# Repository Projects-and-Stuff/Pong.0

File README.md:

# Pong.0 #
#### Capacitive Sensing Beer Pong Gaming Modules ####

Currently developing the prototype of a capacitive-sensing Beer Pong game module.

---

*File Structure*

* ./BPS_Test/ --> The initial Testing board, including Hardware and Firmware folders
* ./Firmware/ --> Firmware for the project (Written in C Utilizing AVR Studio 6 and AVRGCC)
* ./Hardware/ --> KiCad Project for Pong.0 Hardware
* ./GerberOutput/ --> The latest Gerber Files for manufacture
* ./Notes/ --> Project Notes, BOM, and Research

---

Additional information, research, and notes can be found at http://www.projectsandstuff.com, or email us at support@projectsandstuff.com

Let us know if you fork and make improvements. We'd be glad to consider merges that improve this project.

---

UPDATES:

---

CURRENT AUTHORS:

> [Jack Linke](http://www.jacklinke.com)
jacklinke@gmail.com

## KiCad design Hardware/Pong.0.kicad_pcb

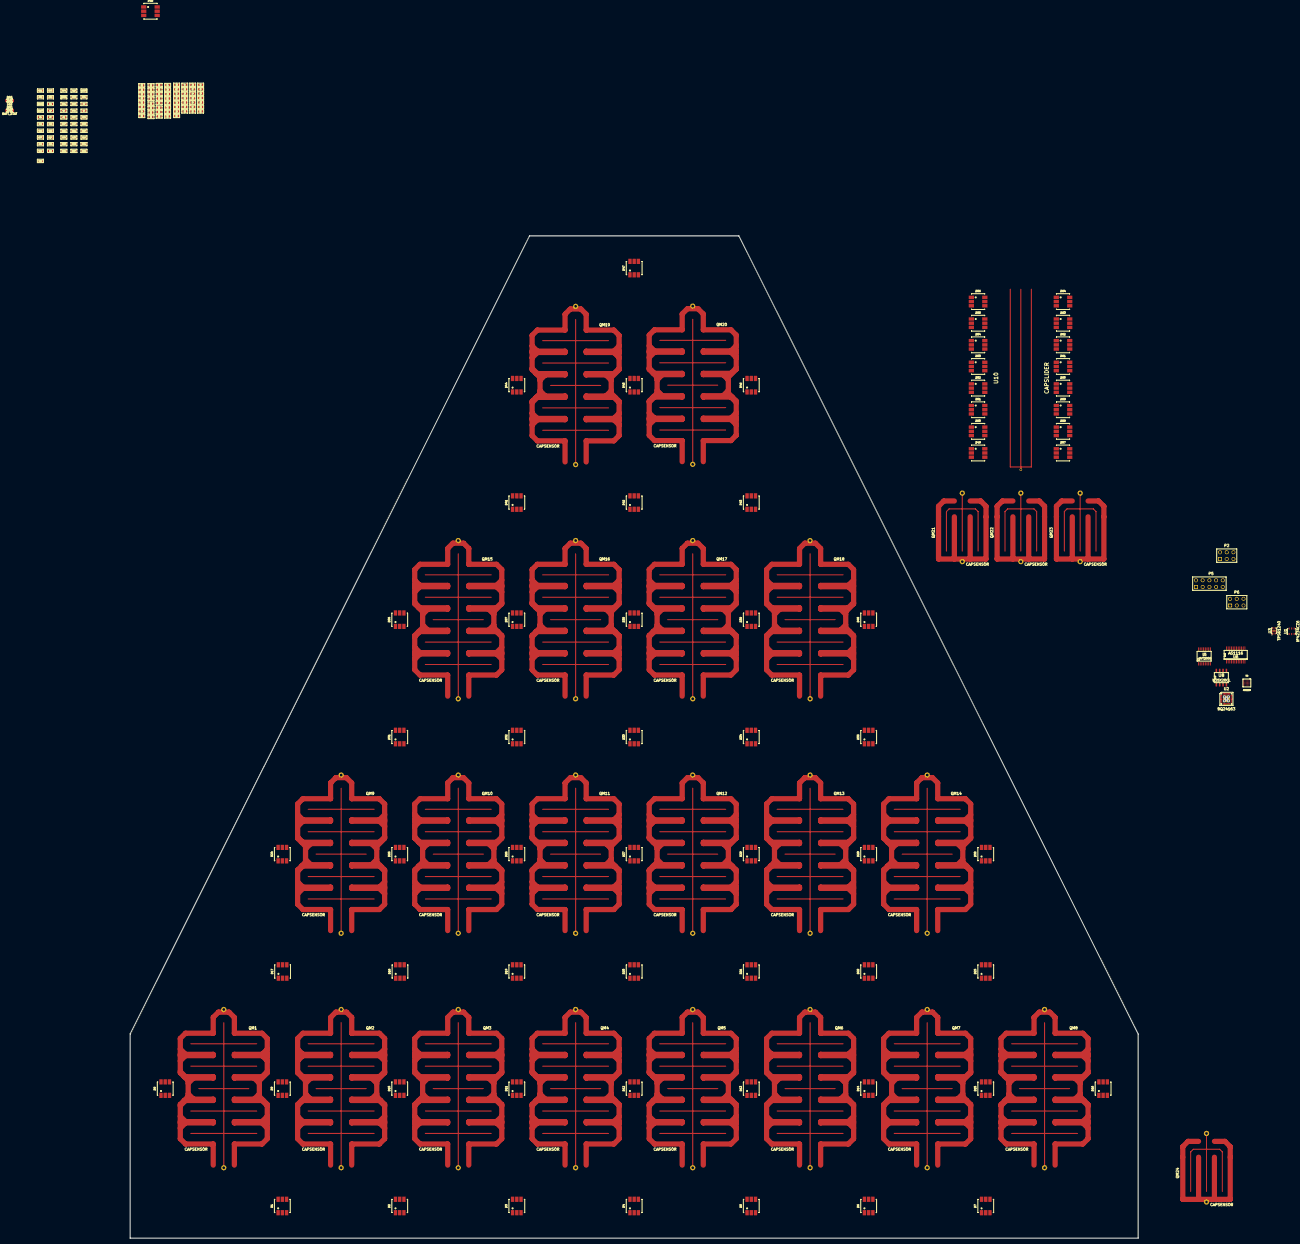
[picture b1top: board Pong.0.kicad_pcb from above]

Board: 2 copper layers, 382.2 x 380.0 mm, 213 parts (0 on the bottom side), 94 nets, no tracks yet.

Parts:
C1: 4.7nF; SM0603
C2, C3, C6, C9, C19, C20, C48: 1uF; SM0603
C4, C5, C11, C12: 4.7uF; SM0603
C7: 0.01uF; SM0603
C8, C13, C15, C17, C44, C51, C58: 10uF; SM0603
C10: CSMALL; SM0603
C14, C16, C18, C43, C45, C46, C47, C52, C53, C54, C55, C56, C57, C59, C60: 0.1uF; SM0603
C21: 2.2uF; SM0603
C22, C23, C24, C25, C26, C27, C29, C30, C31, C32, C33, C34, C36, C37, C38, C39, C40, C41: 1nF; SM0603
C49, C50: 15pF; SM0603
CS0, CS1, CS2, CS3: 4.7nF; SM0603
D1, D2, D3, D4, D5, D6, D7, D8, D9, D10, D11, D12, D13, D14, D15, D16, D17, D18, D19, D20, D21, D22, D23, D24, D25, D26, D27, D28, D29, D30, D31, D32, D33, D34, D35, D36, D37, D38, D39, D40, D41, D42, D43, D44, D45, D46, D47, D48, D49, D50, D51, D52, D53, D54, D55, D56, D57, D58, D59, D60, D61, D62, D63, D64: RGB_LED_V2; PLCC-5050
D65: BATT_STAT; LED-0805
D66: LED; LED-0805
P2: ISP; pin_array_3x2
P5: JTAG; PIN_ARRAY_5x2
P6: PDI; pin_array_3x2
QM1, QM2, QM3, QM4, QM5, QM6, QM7, QM8, QM9, QM10, QM11, QM12, QM13, QM14, QM15, QM16, QM17, QM18, QM19, QM20: CAPSENSOR; Capsensor_35mm_x_60mm
QM21, QM22, QM23, QM24: CAPSENSOR; CapSensor_20mm_x_24mm
R1: 1M; SM0603
R2, R23: R; SM0603
R3: R_HI; SM0603
R4: R_LO; SM0603
R5, R6, R7, R9, R10, R11, R12, R22, R24, R26, R27, R28: 10k; SM0603
R8: 100k; SM0603
R13, R14, R15, R16, R18, R19, R20, R21: 560; SM0603
R17: 200k; SM0603
R25: R_SMALL; SM0603
RS1, RS2, RS3, RS4, RS5, RS6, RS7: 1k; SM0603
RSMP0, RSMP1, RSMP2, RSMP3: 470k; SM0603
RX0, RX1, RX2, RX3, RX4, RX5, RX6, RX7: 1k; SM0603
RY0, RY1, RY2, RY3: 1k; SM0603
U1: IP4234CZ6; SOT457
U2: BQ24163; QFN24
U3: TPS61240; QFN-6
U4: AS1119; WLCSP-36
U5: NVT2006; TSSOP16
U6: AS1116; SSOP24
U8: W25X20CL; SO8E
U10: CAPSLIDER; CapSensor_Slider_16mm_x_66mm

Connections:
/Controller/CTRL_3_3V: C10.1, C11.1, C14.1, C16.1, C18.1, C46.1, C48.1, C60.1, P2.2, P5.4, P6.2, R5.1, R6.1, R7.1, R13.1, R14.1, R15.1, R16.1, U2.13, U2.14, U3.4, U3.6, U4.A6, U4.E1, U4.E5, U5.16, U8.8
/Controller/CTRL_D+: U1.1, U2.2
/Controller/CTRL_D-: U1.6, U2.1
/Controller/CTRL_MISO_1: P2.1, U8.2
/Controller/CTRL_MISO_2: R14.2, U5.3
/Controller/CTRL_MOSI_1: P2.4, U8.5
/Controller/CTRL_MOSI_2: R15.2, U5.2
/Controller/CTRL_SCK_1: P2.3, U8.6
/Controller/CTRL_SCK_2: R16.2, U5.1
/Controller/CTRL_SCL_1: R7.2, U2.3
/Controller/CTRL_SDA_1: R6.2, U2.4
/Controller/CTRL_SMP: RSMP0.2, RSMP1.2, RSMP2.2, RSMP3.2
/Controller/CTRL_Y0A: CS0.1, RY0.2
/Controller/CTRL_Y0B: CS0.2, RSMP0.1
/Controller/CTRL_Y1A: CS1.1, RY1.2
/Controller/CTRL_Y1B: CS1.2, RSMP1.1
/Controller/CTRL_Y2A: CS2.1, RY2.2
/Controller/CTRL_Y2B: CS2.2, RSMP2.1
/Controller/CTRL_Y3A: CS3.1, RY3.2
/Controller/CTRL_Y3B: CS3.2, RSMP3.1
/Controller/CTRL_~SS~_1: P2.5, U8.1
/Controller/CTRL_~SS~_2: R13.2, U5.4
/Controller/PDI_CLK: P5.6, P6.5
/LED_Display/CS0: C36.1, D1.2, D1.3, D1.5, D2.2, D3.2, D4.2, D5.2, D6.2, D7.2, D8.2, D17.1, D17.3, D17.5, D33.1, D33.3, D33.5, U4.A5
/LED_Display/CS1: C38.1, D1.1, D2.3, D2.5, D17.2, D18.2, D18.3, D18.5, D19.2, D20.2, D21.2, D22.2, D23.2, D24.2, D34.1, D34.3, D34.5, U4.A4
/LED_Display/CS2: C40.1, D2.1, D3.3, D3.5, D18.1, D19.3, D19.5, D33.2, D34.2, D35.2, D35.3, D35.5, D36.2, D37.2, D38.2, D39.2, D40.2, U4.A3
/LED_Display/CS3: C29.1, D1.4, D2.4, D3.1, D3.4, D4.4, D4.5, D5.4, D6.4, D7.4, D8.4, D19.1, D20.3, D20.5, D35.1, D36.3, D36.5, U4.B4
/LED_Display/CS4: C31.1, D4.1, D4.3, D5.5, D17.4, D18.4, D19.4, D20.1, D20.4, D21.4, D21.5, D22.4, D23.4, D24.4, D36.1, D37.3, D37.5, U4.B3
/LED_Display/CS5: C33.1, D5.1, D5.3, D6.5, D21.1, D21.3, D22.5, D33.4, D34.4, D35.4, D36.4, D37.1, D37.4, D38.4, D38.5, D39.4, D40.4, U4.B2
/LED_Display/CS6: C22.1, D1.6, D2.6, D3.6, D4.6, D5.6, D6.1, D6.3, D6.6, D7.6, D8.6, D22.1, D22.3, D23.5, D38.1, D38.3, D39.5, U4.C4
/LED_Display/CS7: C24.1, D7.1, D7.3, D7.5, D17.6, D18.6, D19.6, D20.6, D21.6, D22.6, D23.1, D23.3, D23.6, D24.6, D39.1, D39.3, D40.5, U4.C3
/LED_Display/CS8: C26.1, D8.1, D8.3, D8.5, D24.1, D24.3, D24.5, D33.6, D34.6, D35.6, D36.6, D37.6, D38.6, D39.6, D40.1, D40.3, D40.6, U4.C2
/LED_Display/CS9: C37.1, D9.2, D9.3, D9.5, D10.2, D11.2, D12.2, D13.2, D14.2, D15.2, D16.2, D25.1, D25.3, D25.5, D41.1, D41.3, D41.5, U4.D4
/LED_Display/CS10: C39.1, D9.1, D10.3, D10.5, D25.2, D26.2, D26.3, D26.5, D27.2, D28.2, D29.2, D30.2, D31.2, D32.2, D42.1, D42.3, D42.5, U4.D3
/LED_Display/CS11: C41.1, D10.1, D11.3, D11.5, D26.1, D27.3, D27.5, D41.2, D42.2, D43.2, D43.3, D43.5, D44.2, D45.2, D46.2, D47.2, D48.2, U4.D2
/LED_Display/CS12: C30.1, D9.4, D10.4, D11.1, D11.4, D12.4, D12.5, D13.4, D14.4, D15.4, D16.4, D27.1, D28.3, D28.5, D43.1, D44.3, D44.5, U4.E4
/LED_Display/CS13: C32.1, D12.1, D12.3, D13.5, D25.4, D26.4, D27.4, D28.1, D28.4, D29.4, D29.5, D30.4, D31.4, D32.4, D44.1, D45.3, D45.5, U4.E3
/LED_Display/CS14: C34.1, D13.1, D13.3, D14.5, D29.1, D29.3, D30.5, D41.4, D42.4, D43.4, D44.4, D45.1, D45.4, D46.4, D46.5, D47.4, D48.4, U4.E2
/LED_Display/CS15: C23.1, D9.6, D10.6, D11.6, D12.6, D13.6, D14.1, D14.3, D14.6, D15.6, D16.6, D30.1, D30.3, D31.5, D46.1, D46.3, D47.5, U4.F4
/LED_Display/CS16: C25.1, D15.1, D15.3, D15.5, D25.6, D26.6, D27.6, D28.6, D29.6, D30.6, D31.1, D31.3, D31.6, D32.6, D47.1, D47.3, D48.5, U4.F3
/LED_Display/CS17: C27.1, D16.1, D16.3, D16.5, D32.1, D32.3, D32.5, D41.6, D42.6, D43.6, D44.6, D45.6, D46.6, D47.6, D48.1, D48.3, D48.6, U4.F2
/LED_Display_B/DIG0: D49.2, D50.2, D51.2, D52.2, D53.2, D54.2, D55.2, D56.2, U6.2
/LED_Display_B/DIG1: D57.2, D58.2, D59.2, D60.2, D61.2, D62.2, D63.2, D64.2, U6.3
/LED_Display_B/DIG2: D49.4, D50.4, D51.4, D52.4, D53.4, D54.4, D55.4, D56.4, U6.4
/LED_Display_B/DIG3: D57.4, D58.4, D59.4, D60.4, D61.4, D62.4, D63.4, D64.4, U6.5
/LED_Display_B/DIG4: D49.6, D50.6, D51.6, D52.6, D53.6, D54.6, D55.6, D56.6, U6.7
/LED_Display_B/DIG5: D57.6, D58.6, D59.6, D60.6, D61.6, D62.6, D63.6, D64.6, U6.8
/LED_Display_B/DISP_B_5V: C12.1, C45.1, R17.1, U3.2, U3.3, U6.19
/LED_Display_B/SEGA: D49.1, D49.3, D49.5, D57.1, D57.3, D57.5, U6.15
/LED_Display_B/SEGB: D50.1, D50.3, D50.5, D58.1, D58.3, D58.5, U6.17
/LED_Display_B/SEGC: D51.1, D51.3, D51.5, D59.1, D59.3, D59.5, U6.20
/LED_Display_B/SEGD: D52.1, D52.3, D52.5, D60.1, D60.3, D60.5, U6.23
/LED_Display_B/SEGE: D53.1, D53.3, D53.5, D61.1, D61.3, D61.5, U6.21
/LED_Display_B/SEGF: D54.1, D54.3, D54.5, D62.1, D62.3, D62.5, U6.16
/LED_Display_B/SEGG: D55.1, D55.3, D55.5, D63.1, D63.3, D63.5, U6.18
/LED_Display_B/SEGH: D56.1, D56.3, D56.5, D64.1, D64.3, D64.5, U6.22
/PowerManagement/VDRV: C6.1, D65.1, R3.1, U2.6
GND: C1.2, C2.2, C3.2, C4.2, C5.2, C6.2, C9.2, C10.2, C11.2, C12.2, C14.2, C16.2, C18.2, C21.1, C22.2, C23.2, C24.2, C25.2, C26.2, C27.2, C29.2, C30.2, C31.2, C32.2, C33.2, C34.2, C36.2, C37.2, C38.2, C39.2, C40.2, C41.2, C43.2, C45.2, C46.2, C47.2, C48.2, C49.2, C50.2, C52.2, C53.2, C54.2, C55.2, C56.2, C57.2, C58.2, C59.2, C60.2, P2.6, P5.2, P5.10, P6.6, R1.2, R4.2, R23.2, U1.2, U2.5, U2.15, U2.16, U2.17, U2.24, U3.1, U3.GNDP, U4.A2, U4.B5, U4.C5, U4.D5, U4.F5, U5.5, U5.6, U5.7, U5.8, U5.15, U6.6, U8.4
unnamed: C20.2, U4.D1
unnamed: C20.1, U4.A1
unnamed: C19.2, U4.C1
unnamed: C19.1, U4.B1
unnamed: C21.2, U4.F1
unnamed: C1.1, R1.1
unnamed: C9.1, U2.11, U2.12
unnamed: C5.1, U2.23
unnamed: R3.2, R4.1, U2.9
unnamed: R5.2, R8.1, U2.7
unnamed: C7.2, U2.19
unnamed: C2.1, U2.21
unnamed: R2.2, U2.8
unnamed: D65.2, R2.1
unnamed: C3.1, U1.5, U2.22
unnamed: C7.1, U2.18
unnamed: C4.1, U2.20
unnamed: QM9.Y, QM10.Y, QM11.Y, QM12.Y, QM13.Y, QM14.Y, QM15.Y, QM16.Y, RY1.1
unnamed: QM1.Y, QM2.Y, QM3.Y, QM4.Y, QM5.Y, QM6.Y, QM7.Y, QM8.Y, RY0.1
unnamed: RY3.1, U10.Y
unnamed: QM1.X, QM9.X, QM17.X, RS1.1, RX0.2, U10.X8
unnamed: QM2.X, QM10.X, QM18.X, RS1.2, RS2.1, RX1.2, U10.X7
unnamed: QM3.X, QM11.X, QM19.X, RS2.2, RS3.1, RX2.2, U10.X6
unnamed: QM4.X, QM12.X, QM20.X, RS3.2, RS4.1, RX3.2, U10.X5
unnamed: QM5.X, QM13.X, QM21.X, RS4.2, RS5.1, RX4.2, U10.X4
unnamed: QM6.X, QM14.X, QM22.X, RS5.2, RS6.1, RX5.2, U10.X3
unnamed: QM7.X, QM15.X, QM23.X, RS6.2, RS7.1, RX6.2, U10.X2
unnamed: QM8.X, QM16.X, QM24.X, RS7.2, RX7.2, U10.X1
unnamed: QM17.Y, QM18.Y, QM19.Y, QM20.Y, QM21.Y, QM22.Y, QM23.Y, QM24.Y, RY2.1
unnamed: C52.1, C53.1, C54.1, C55.1, C56.1
unnamed: C57.1, C58.1
unnamed: R18.2, U5.12, U6.14
unnamed: R20.2, U5.10, U6.24
unnamed: R19.2, U5.11, U6.1
unnamed: R21.2, U5.9, U6.11
unnamed: C43.1, R17.2, R18.1, R19.1, R20.1, R21.1, U5.13, U5.14

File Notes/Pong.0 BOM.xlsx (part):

Bill of Materials - Pong.0 - Electronics |  |  |  |  |  |  |  |  |  | # of boards goal: | 500
Projects and Stuff LLC - http://www.projectsandstuff.com
Total BOM Parts Cost: | 15529.26 | Part Cost Per Board: |  | 31.058520000000001
Description | Mfg Part # | Package | KiCad Footprint | Default Supplier | Supplier On Hand | Qty per board | Total Qty Needed | Price per part at Qty | Total Price | Notes | Part References
IC Atmel AVR XMEGA16A4U | ATXMEGA16A4U-AUR | 44-TQFP |  | DigiKey | 3483 | 1 | 500 | 2.0038999999999998 | 1001.9499999999999
IC Level Translator | NVT2006PW,118 | 16-TSSOP |  | DigiKey | 7348 | 1 | 500 | 0.49 | 245 | SPI/I2C translation for the LED Drivers
PLCC-6 RGB LED |  | 5mm x 5mm |  |  |  | 64 | 32000 | 0.04 | 1280 | LED Lighting
Capacitor Ceramic 15pF | CL10C150JB8NCNC | 0603 |  | DigiKey | 6750 | 2 | 1000 | 3.0899999999999999E-3 | 3.09 |  | C49, C50
Capacitor Ceramic 1nF | CL10B102KB8SFNC | 0603 |  | DigiKey | 24000 | 20 | 10000 | 2.3700000000000001E-3 | 23.700000000000003 |  | C22, C23, C24, C25, C26, C27, C28, C29, C30, C31, C32, C33, C34, C35, C36, C37,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
Capacitor Ceramic 4.7nF | CL10B472KB8SFNC | 0603 |  | DigiKey | 8862 | 5 | 2500 | 6.1799999999999997E-3 | 15.45 |  | C1, CS0, CS1, CS2, CS3
Capacitor Ceramic 0.01uF | CL10B103MB8NCNC | 0603 |  | DigiKey | 7910 | 1 | 500 | 2.7799999999999999E-3 | 1.39 |  | C7
Capacitor Ceramic 0.1uF 50V 10% | CL10B104KO8NNNC | 0603 |  | DigiKey | 3308000 | 15 | 7500 | 3.5899999999999999E-3 | 26.925000000000001 | Used for Power Input/Output filtering and Decoupling | C14, C16, C18, C43, C45, C46, C47, C52, C53, C54, C55, C56, C57, C59, C60
Capacitor Ceramic 1uF | LMK107B7105KA-T | 0603 |  | DigiKey | 76000 | 7 | 3500 | 7.8200000000000006E-3 | 27.37 |  | C2, C3, C6, C9, C19, C20, C48
Capacitor Ceramic 2.2uF | LMK107B7225KA-T | 0603 |  | DigiKey | 217168 | 1 | 500 | 3.8519999999999999E-2 | 19.259999999999998 |  | C21
Capacitor Ceramic 4.7uF | C1608X7S1A475M080AC | 0603 |  | DigiKey | 1179 | 4 | 2000 | 6.1199999999999997E-2 | 122.39999999999999 |  | C4, C5, C11, C12
Capacitor Ceramic 10uF | C1608X7S0J106M080AC | 0603 |  | Digikey | 4000 | 7 | 3500 | 0.26812999999999998 | 938.45499999999993 | Used for Supply Filtering (Input and Output). Low ESR | C8, C13, C15, C17, C44, C51, C58
Resistor 560 Ohm | ERJ-3GEYJ561V | 0603 |  | DigiKey | 155000 | 8 | 4000 | 1.5200000000000001E-3 | 6.08 | Cheaper to buy 5000 | R13, R14, R15, R16, R18, R19, R20, R21
Resistor 1k | MCR03EZP5J102 | 0603 |  | DigiKey | 1365000 | 18 | 9000 | 1.1999999999999999E-3 | 10.799999999999999 | Cheaper to buy 10000 | RX0, RX1, RX2, RX3, RX4, RX5, RX6, RX7, RS1, RS2, RS3, RS4, RS5, RS6, RY0, RY1,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
Resistor 10k | ERJ-3GEYJ103V | 0603 |  | DigiKey | 8283494 | 12 | 6000 | 2.5600000000000002E-3 | 15.360000000000001 |  | R5, R6, R7, R9, R10, R11, R12, R22, R24, R26, R27, R28
Resistor 100k | RC1608J104CS | 0603 |  | DigiKey | 20673 | 1 | 500 | 2.7399999999999998E-3 | 1.3699999999999999 |  | R8
Resisitor 200k | RC1608J204CS | 0603 |  | DigiKey | 20000 | 1 | 500 | 2.7399999999999998E-3 | 1.3699999999999999 |  | R17
Resistor 470k | ERJ-3EKF4703V | 0603 |  | DigiKey | 299269 | 4 | 2000 | 3.8400000000000001E-3 | 7.6800000000000006 |  | RSMP0, RSMP1, RSMP2, RSMP3
Resistor 1M | RC1608J105CS | 0603 |  | DigiKey | 12666 | 1 | 500 | 2.7399999999999998E-3 | 1.3699999999999999 |  | R1
LED Red Diffused | LH R974-LP-1 | 0805 |  | DigiKey | 43194 | 1 | 500 | 4.3700000000000003E-2 | 21.85 | Power Indicator
LED Green Diffused | LG N971-KN-1 | 0805 |  | DigiKey | 94327 | 1 | 500 | 4.3700000000000003E-2 | 21.85 | Status Indicator
IC Boost Regulator 5V 0.45A | TPS61240DRVT | 6-WDFN |  | DigiKey | 51750 | 1 | 500 | 0.9425 | 471.25 | 5V Power for LEDs and Drivers
IC 64 LED Driver | AS1116-BSST | 24-QSOP |  | DigiKey | 12727 | 1 | 500 | 3.7223600000000001 | 1861.18 | SPI LED Driver
IC LED Matrix Driver | AS1119-BWLT | 36-WLCSP |  | DigiKey | 2326 | 1 | 500 | 5.7294200000000002 | 2864.71
USB Connector | ZX62WRD-B-5PC | USB Micro B |  | DigiKey | 5213 | 1 | 500 | 0.83160000000000001 | 415.8 | Water Resistant Micro B USB Connector
IC RF Transceiver | CC2500RTKR | 20-VFQFN |  | DigiKey | 15533 | 1 | 500 | 1.56 | 780 | 2.4GHz Transceiver
26 MHz Crystal | ABM8G-26.000MHZ-4Y-T3 | 4-SMD |  | DigiKey | 6517 | 1 | 500 | 0.51300000000000001 | 256.5 | Reference Crystal for RF Chip CC2500
IC Battery Manager/Charger | BQ24163RGET | 24-VFQFN |  | DigiKey | 706 | 1 | 500 | 2.6324999999999998 | 1316.25
IC USB ESD Protection | IP4234CZ6,125 | 6-TSOP |  | DigiKey | 8164 | 1 | 500 | 0.21565999999999999 | 107.83
LI Battery |  |  |  |  |  | 1 | 500 | 7 | 3500
IC Flash Memory 2Mbit | W25X20CLSNIG | 8-SOIC |  | DigiKey | 7531 | 1 | 500 | 0.32604 | 163.02000000000001
 |  |  |  |  |  |  | 0 |  | 0
 |  |  |  |  |  |  | 0 |  | 0
 |  |  |  |  |  |  | 0 |  | 0
 |  |  |  |  |  |  | 0 |  | 0
 |  |  |  |  |  |  | 0 |  | 0
 |  |  |  |  |  |  | 0 |  | 0
 |  |  |  |  |  |  | 0 |  | 0
 |  |  |  |  |  |  | 0 |  | 0
 |  |  |  |  |  |  | 0 |  | 0
 |  |  |  |  |  |  | 0 |  | 0
 |  |  |  |  |  |  | 0 |  | 0
 |  |  |  |  |  |  | 0 |  | 0
 |  |  |  |  |  |  | 0 |  | 0
 |  |  |  |  |  |  | 0 |  | 0
 |  |  |  |  |  |  | 0 |  | 0
 |  |  |  |  |  |  | 0 |  | 0
 |  |  |  |  |  |  | 0 |  | 0
 |  |  |  |  |  |  | 0 |  | 0
 |  |  |  |  |  |  | 0 |  | 0
 |  |  |  |  |  |  | 0 |  | 0
 |  |  |  |  |  |  | 0 |  | 0
 |  |  |  |  |  |  | 0 |  | 0
 |  |  |  |  |  |  | 0 |  | 0
 |  |  |  |  |  |  | 0 |  | 0
 |  |  |  |  |  |  | 0 |  | 0
 |  |  |  |  |  |  | 0 |  | 0
 |  |  |  |  |  |  | 0 |  | 0
 |  |  |  |  |  |  | 0 |  | 0
 |  |  |  |  |  |  | 0 |  | 0
 |  |  |  |  |  |  | 0 |  | 0
 |  |  |  |  |  |  | 0 |  | 0
 |  |  |  |  |  |  | 0 |  | 0
 |  |  |  |  |  |  | 0 |  | 0
 |  |  |  |  |  |  | 0 |  | 0
 |  |  |  |  |  |  | 0 |  | 0
 |  |  |  |  |  |  | 0 |  | 0
 |  |  |  |  |  |  | 0 |  | 0
 |  |  |  |  |  |  | 0 |  | 0
 |  |  |  |  |  |  | 0 |  | 0
 |  |  |  |  |  |  | 0 |  | 0
 |  |  |  |  |  |  | 0 |  | 0
 |  |  |  |  |  |  | 0 |  | 0
 |  |  |  |  |  |  | 0 |  | 0
 |  |  |  |  |  |  | 0 |  | 0
 |  |  |  |  |  |  | 0 |  | 0
 |  |  |  |  |  |  | 0 |  | 0
 |  |  |  |  |  |  | 0 |  | 0
 |  |  |  |  |  |  | 0 |  | 0
 |  |  |  |  |  |  | 0 |  | 0
 |  |  |  |  |  |  | 0 |  | 0
 |  |  |  |  |  |  | 0 |  | 0
 |  |  |  |  |  |  | 0 |  | 0
 |  |  |  |  |  |  | 0 |  | 0
 |  |  |  |  |  |  | 0 |  | 0
 |  |  |  |  |  |  | 0 |  | 0
 |  |  |  |  |  |  | 0 |  | 0
 |  |  |  |  |  |  | 0 |  | 0
 |  |  |  |  |  |  | 0 |  | 0
 |  |  |  |  |  |  | 0 |  | 0
 |  |  |  |  |  |  | 0 |  | 0
 |  |  |  |  |  |  | 0 |  | 0
 |  |  |  |  |  |  | 0 |  | 0
 |  |  |  |  |  |  | 0 |  | 0
 |  |  |  |  |  |  | 0 |  | 0
 |  |  |  |  |  |  | 0 |  | 0
 |  |  |  |  |  |  | 0 |  | 0
 |  |  |  |  |  |  | 0 |  | 0
 |  |  |  |  |  |  | 0 |  | 0
 |  |  |  |  |  |  | 0 |  | 0
 |  |  |  |  |  |  | 0 |  | 0
 |  |  |  |  |  |  | 0 |  | 0
 |  |  |  |  |  |  | 0 |  | 0
 |  |  |  |  |  |  | 0 |  | 0
 |  |  |  |  |  |  | 0 |  | 0
 |  |  |  |  |  |  | 0 |  | 0
 |  |  |  |  |  |  | 0 |  | 0
 |  |  |  |  |  |  | 0 |  | 0
 |  |  |  |  |  |  | 0 |  | 0
 |  |  |  |  |  |  | 0 |  | 0
 |  |  |  |  |  |  | 0 |  | 0
 |  |  |  |  |  |  | 0 |  | 0
 |  |  |  |  |  |  | 0 |  | 0
 |  |  |  |  |  |  | 0 |  | 0
 |  |  |  |  |  |  | 0 |  | 0
 |  |  |  |  |  |  | 0 |  | 0
 |  |  |  |  |  |  | 0 |  | 0
 |  |  |  |  |  |  | 0 |  | 0
 |  |  |  |  |  |  | 0 |  | 0
 |  |  |  |  |  |  | 0 |  | 0
 |  |  |  |  |  |  | 0 |  | 0
 |  |  |  |  |  |  | 0 |  | 0
 |  |  |  |  |  |  | 0 |  | 0
 |  |  |  |  |  |  | 0 |  | 0
 |  |  |  |  |  |  | 0 |  | 0
 |  |  |  |  |  |  | 0 |  | 0
 |  |  |  |  |  |  | 0 |  | 0
 |  |  |  |  |  |  | 0 |  | 0
 |  |  |  |  |  |  | 0 |  | 0
 |  |  |  |  |  |  | 0 |  | 0
 |  |  |  |  |  |  | 0 |  | 0
 |  |  |  |  |  |  | 0 |  | 0
 |  |  |  |  |  |  | 0 |  | 0
 |  |  |  |  |  |  | 0 |  | 0
 |  |  |  |  |  |  | 0 |  | 0
 |  |  |  |  |  |  | 0 |  | 0
 |  |  |  |  |  |  | 0 |  | 0
 |  |  |  |  |  |  | 0 |  | 0
 |  |  |  |  |  |  | 0 |  | 0
 |  |  |  |  |  |  | 0 |  | 0
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
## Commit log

2012-03-15 First commit. Adding Readme
2012-03-15 updating initial files
2012-03-15 updating initial KiCad Project for Test Bord
2012-04-09 Adding Note Files to start low-level documentation prep
2012-04-09 Small updates to BOM. Will improve soon
2012-04-22 Updated README.md for the test board
2012-04-22 Created basic Sketchup image to describe the basic layout prior to prototyping
2012-04-22 Corrected sketch (removed an extraneous line)
2012-04-22 Began working BOM for test board, which will eventually supplement/supersede previously posted BOM for main project
2012-04-25 Started building up BOM based on known needs
2012-04-25 Began building documentation
2012-04-26 Updated Project Log. Updated BOM with additional microcontroller data
2012-04-29 Updated Project log based on most recent behind-the-scenes work
2012-04-29 Quick BOM update with details about desired battery specifications
2012-04-29 Updated the Project Log with more info about batteries
2012-04-29 Removed Charge Manager and updated Battery Specs in BOM
2012-04-29 Cleaned up Notes folder
2012-05-02 Updated BOM and Project Log with new choice of LDO regulator
2012-05-03 Major additions to BOM and began Schematics in earnest!
2012-05-03 Corrected Display matrix problem
2012-05-05 Fleshed out schematics some more. Updated Project Log and BOM
2012-05-05 Updated display matrix to better reflect final project goals
2012-05-05 Whoops - Fixed goofy mistake in the display matrix
2012-05-05 Updated Schematic PDF
2012-05-06 Updated BOM, Project Log, and Schematic PDF, and improved schematic details
2012-05-06 Updated Project Log with notes about batteries
2012-05-06 Relocated Schematic PDF to Hardware folder
2012-05-07 Added new BOM format
2012-05-12 Cleaned up Schematics
2012-05-16 Removed BOM.txt in favor of Excel formatted BOM
2012-05-17 Updated BOM with additional sheet for non-electronic parts
2012-05-19 Updated Repository name and filenames
2012-05-19 Updated more filenames and added initial firmware skeleton
2012-05-20 Slight updates to Project Log
2012-05-29 Removed BOM.txt in preference of BOM spreadsheet
2012-06-02 Updated Schematic and Project Log
2012-06-12 Updated Project Log
2012-07-04 Updated Project Log and added ATTiny84A for slider board testing
2012-07-04 Replaced ATTiny84 with ATMega168 for the added pins and peripherals
2012-08-15 Fleshed out main project, corrected errors, updated Project Log
2012-08-17 Started fleshing out slider portion of the test board schematics
2012-08-17 Forgot to include updated Project Log in last push
2012-08-20 Updated Slider and Project Log
2012-08-26 Cleaned up schematics and added footprint column to BOM. Yet to be populated
2012-09-12 Updated Schematics with LED indicators and cleanup and updated Project Log
2013-01-01 Cleaned up schematics and corrected crystal load capacitor calculation error (should be 36pF vice 9pF)
2013-01-01 Associated some parts with correct modules, and began PCB creation.
2013-01-03 Added 2 buttons and continued organizing PCB.
2013-09-02 Finally making some updates. Beginning work on requirements
2013-09-06 Updated BOM and Requirements Document
2013-09-06 Updated Schematic - Very basic so far
2013-09-06 Updated BOM and Schematic with significant components
2013-09-08 Updated Schematic with Battery Manager and updated some uC pins
2013-09-08 Added sheet for QMatrix Sensors and Sliders
2013-09-09 Added logos, continued updating schematics.
2013-09-09 Added items from Schematics to BOM.
2013-09-09 Replaced Firmware folder contents with beginning code that reflects the newer schematics.
2013-09-09 Performed first Firmware Build (not actually usable)
2013-09-12 Updated LED Display Sheet
2013-09-12 Added Slider. Imported Sheet Pins. Made other minor adjustments to schematics.
2013-09-19 Continued populating the schematics.
2013-09-19 Corrected LED_Display pins
2013-09-19 Generated new Schematic PDF.
2013-09-19 Added new Winbond Flash Memory chip
2013-09-19 Corrected Flash chip version and modified pins.
2013-09-20 Completed Display Wiring Matrix
2013-09-20 To simplify understanding of sensors/sliders, combined into one page
2013-09-20 Removed Slider page (already consolidated to Sensor page)
2013-09-20 Updated pin labels and names
2013-09-20 Updated Schematic Page Order to make a bit more sense
2013-09-20 Cleaned up RF Schematic Page
2013-09-24 Updated from ATXMEGA64A4U to ATXMEGA64A3U
2013-09-24 Added Dipole Antenna
2013-09-24 Non-critical changes
2013-09-25 Corrected Label Names
2013-09-25 Corrected R_SMALL Reference from U? to R?
2013-09-25 Added devices and corrected pins and labels
2013-09-25 Minor Cosmetic Changes
2013-09-25 Began connecting major functional blocks
2013-09-25 Updated pin names
2013-09-25 Created new small polarized capacitor component
2013-09-25 Completed schematic page
2013-09-25 Minor misc changes
2013-09-26 Finalized pin placement/layout
2013-09-26 Fine-tuned some pins and labels
2013-09-26 Cleaned up layout, and finalized pins
2013-09-26 Annotated Schematics
2013-09-26 Made corrections based on ERC results
2013-09-26 Minot cosmetic changes
2013-09-26 Generated Netlist
2013-09-26 Began Placement of components on PCB
2013-09-27 Updated resistors and capacitors on BOM
2013-09-29 Continued updating BOM
2013-10-20 Began working out PCB Dimensions
2014-02-09 Created Module and added sensors
2014-02-09 Added sensors and LEDs to PCB, and began dimensioning board
2014-02-13 Continued layout of PCB
2014-02-22 Added slider, more capacitive sensors, and several ICs. Continuing board layout.
